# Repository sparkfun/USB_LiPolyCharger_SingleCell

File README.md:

Power_Cell_Lipo_Charger_Booster
===============================
[ 
*USB LiPoly Charger- Single Cell (PRT-12711)*](https://www.sparkfun.com/products/12711)

This is a basic charging circuit that allows you to charger 3.7V LiPo cells at a rate of 500mA or 100mA.
It has a selectable solder jumper, USB input, two pre-installed JST connectors and a barrel jack connector. 

Repository Contents
-------------------

* **/Hardware** - All Eagle design files (.brd, .sch, .STL)
* **/Production** - Test bed files and production panel files

License Information
-------------------
The hardware is released under [Creative Commons ShareAlike 4.0 International](https://creativecommons.org/licenses/by-sa/4.0/).

Distributed as-is; no warranty is given.

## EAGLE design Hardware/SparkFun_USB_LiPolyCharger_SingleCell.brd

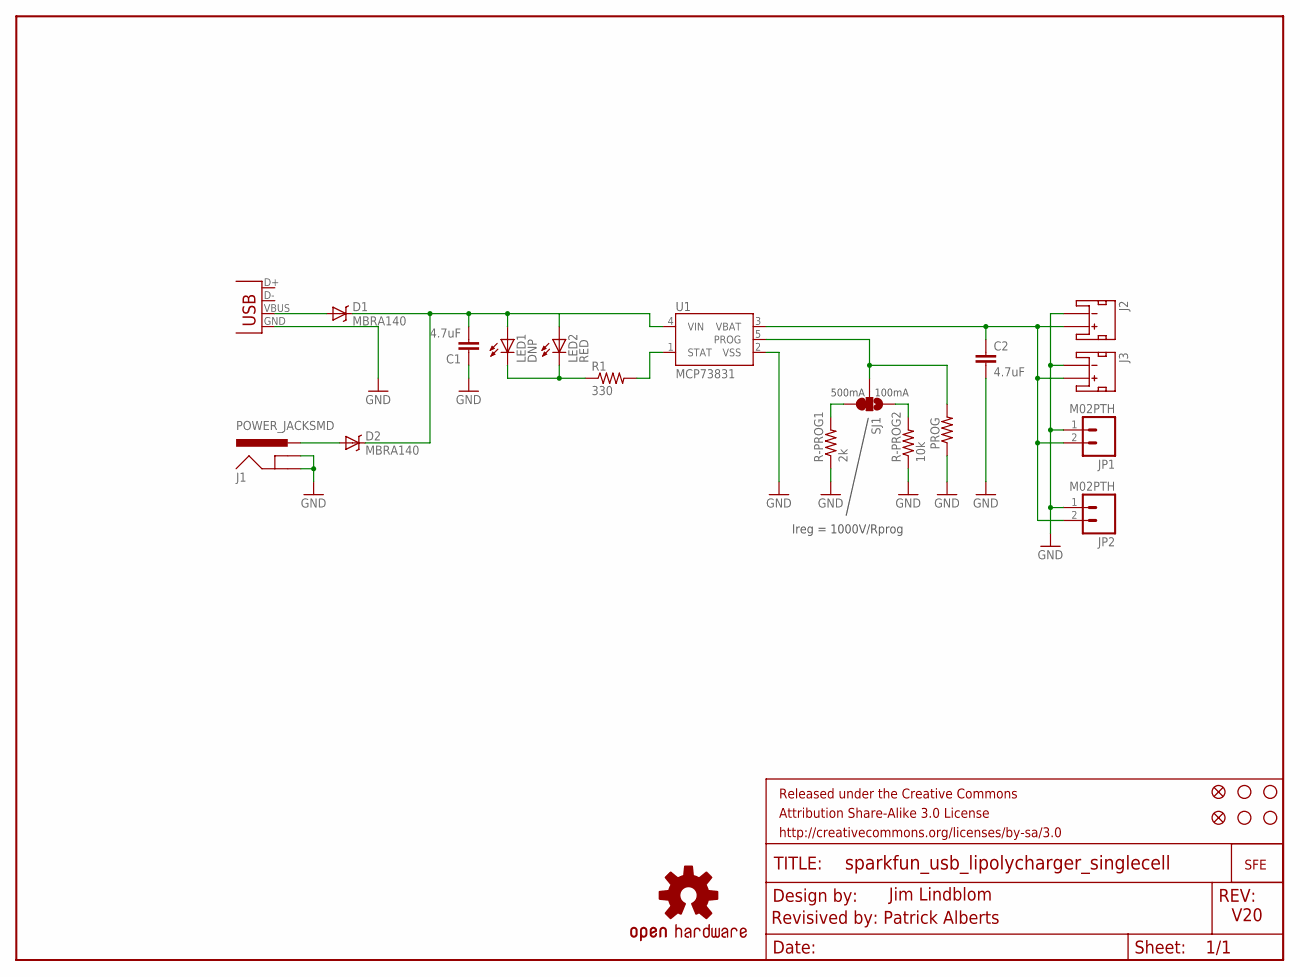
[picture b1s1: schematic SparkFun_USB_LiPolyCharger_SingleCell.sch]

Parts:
C1, C2: 4.7uF; 0603-CAP
D1, D2: MBRA140; SMA-DIODE
FRAME1: FRAME-LETTER; CREATIVE_COMMONS
J1: POWER_JACKSMD; POWER_JACK_SMD
J2, J3: JST_2MM_MALE; JST-2-SMD
JP1, JP2: M02PTH; 1X02
JP7, JP8, JP9, JP10: STAND-OFF
JP11: LOGO-SFENEW; SFE-NEW-WEBLOGO
JP12, JP13: FIDUCIAL1X2; FIDUCIAL-1X2
LED1: DNP; LED3MM
LED2: RED; LED-0603
LOGO1: OSHW-LOGOS; OSHW-LOGO-S
PROG: RESISTORAXIAL-0.3; AXIAL-0.3
R1: 330; 0603-RES
R-PROG1: 2k; 0603-RES
R-PROG2: 10k; 0603-RES
SJ1: SOLDERJUMPER_2WAYS; SJ_3
U1: MCP73831; SOT23-5
X1: USBSMD; USB-MINIB

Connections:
GND: C1.1, C2.2, J1.GND (GNDBREAK), J1.P$4 (GND), J2.1 (-), J3.1 (-), JP1.1, JP2.1, PROG.P$1 (1), R-PROG1.1, R-PROG2.1, U1.2 (VSS), X1.GND
unnamed: C1.2, D1.C, D2.C, LED1.A, LED2.A, U1.4 (VIN)
unnamed: R1.2, U1.1 (STAT)
unnamed: LED1.K (C), LED2.C, R1.1
unnamed: R-PROG1.2, SJ1.3
unnamed: D1.A, X1.VBUS
unnamed: R-PROG2.2, SJ1.1
unnamed: D2.A, J1.VIN0 (PWR)
unnamed: C2.1, J2.2 (+), J3.2 (+), JP1.2, JP2.2, U1.3 (VBAT)
PROG: PROG.P$2 (2), SJ1.2, U1.5 (PROG)

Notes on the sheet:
500mA
100mA
Ireg = 1000V/Rprog
Jim Lindblom
Revisived by: Patrick Alberts
V20

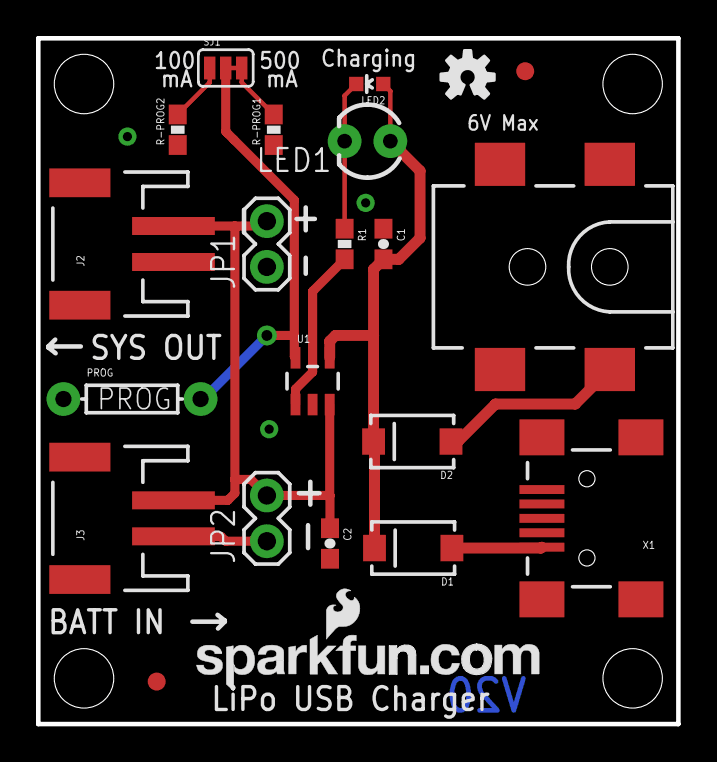
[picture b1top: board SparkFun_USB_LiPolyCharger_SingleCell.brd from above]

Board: 2 copper layers, 35.6 x 38.1 mm, 27 parts (0 on the bottom side), 10 nets.

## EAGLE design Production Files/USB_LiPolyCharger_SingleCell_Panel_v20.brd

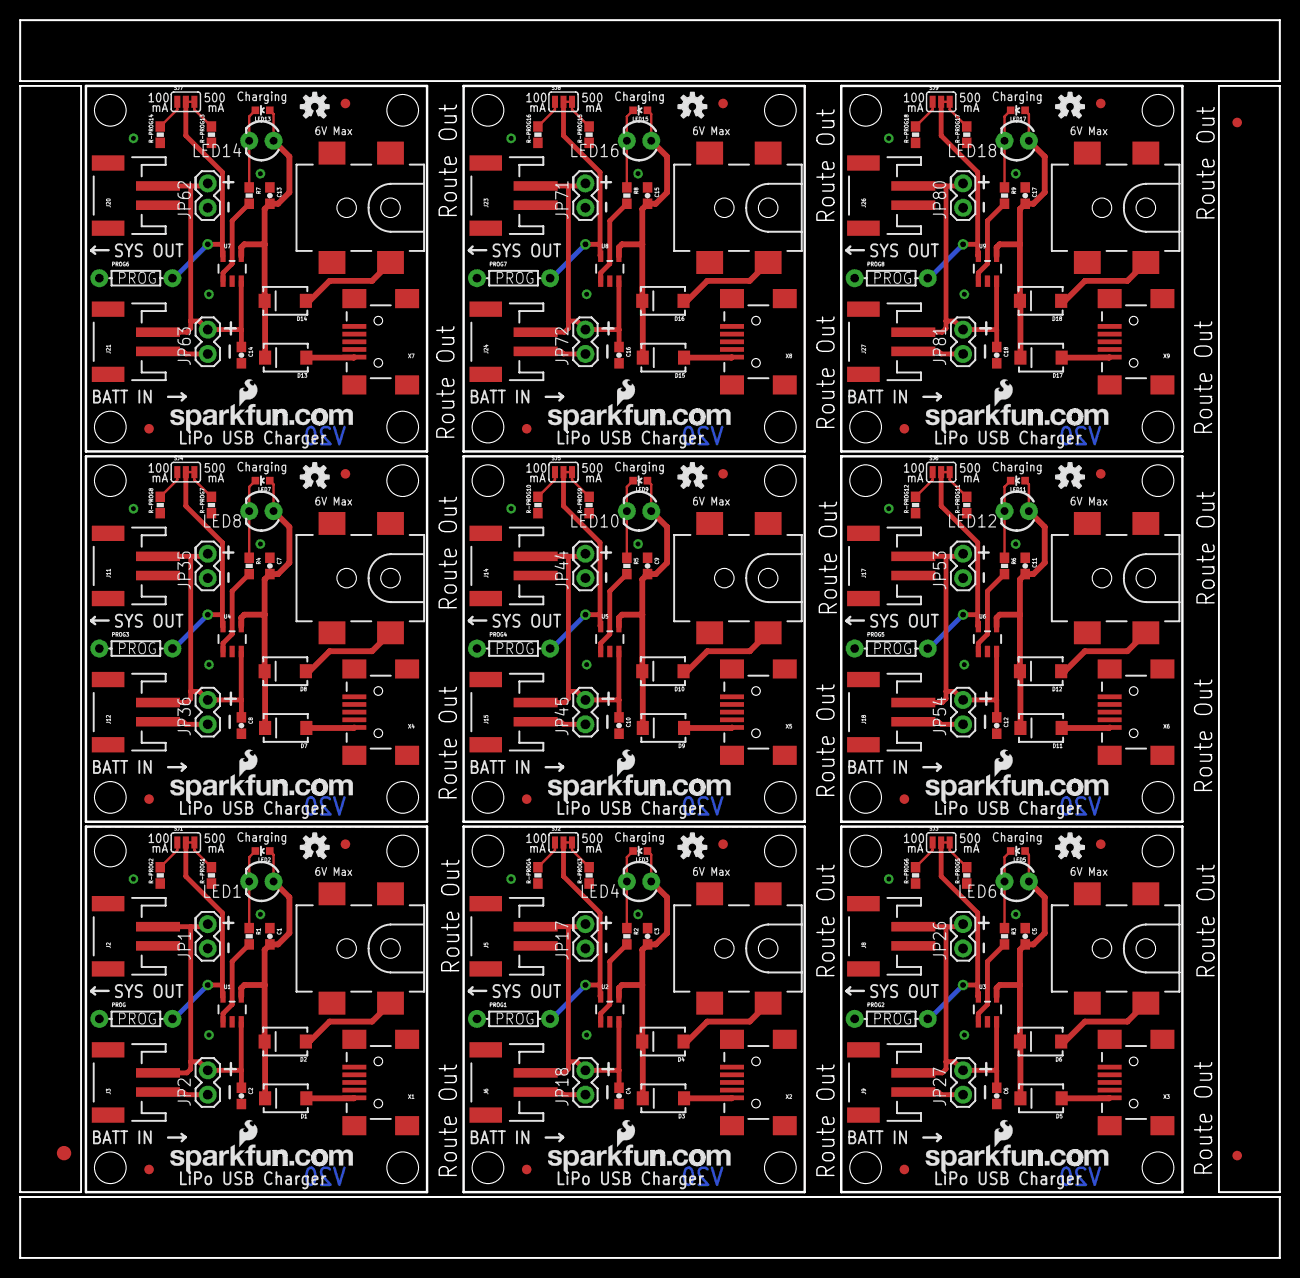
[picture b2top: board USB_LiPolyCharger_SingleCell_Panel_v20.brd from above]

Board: 2 copper layers, 131.3 x 129.0 mm, 237 parts (0 on the bottom side), 90 nets.

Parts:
C1, C2, C3, C4, C5, C6, C7, C8, C9, C10, C11, C12, C13, C14, C15, C16, C17, C18: 4.7uF; 0603-CAP
D1, D2, D3, D4, D5, D6, D7, D8, D9, D10, D11, D12, D13, D14, D15, D16, D17, D18: MBRA140; SMA-DIODE
E$1: FIDUCIAL-1.5X3
E$4, E$5: FIDUCIAL-1X2
J1, J4, J7, J10, J13, J16, J19, J22, J25: POWER_JACKSMD; POWER_JACK_SMD
J2, J3, J5, J6, J8, J9, J11, J12, J14, J15, J17, J18, J20, J21, J23, J24, J26, J27: JST-2-SMD
JP1, JP2, JP17, JP18, JP26, JP27, JP35, JP36, JP44, JP45, JP53, JP54, JP62, JP63, JP71, JP72, JP80, JP81: M02PTH; 1X02
JP3, JP4, JP5, JP6, JP7, JP8, JP9, JP10, JP19, JP20, JP21, JP22, JP28, JP29, JP30, JP31, JP37, JP38, JP39, JP40, JP46, JP47, JP48, JP49, JP55, JP56, JP57, JP58, JP64, JP65, JP66, JP67, JP73, JP74, JP75, JP76: STAND-OFF
JP11, JP14, JP23, JP32, JP41, JP50, JP59, JP68, JP77: LOGO-SFENEW; SFE-NEW-WEBLOGO
JP12, JP13, JP15, JP16, JP24, JP25, JP33, JP34, JP42, JP43, JP51, JP52, JP60, JP61, JP69, JP70, JP78, JP79: FIDUCIAL1X2; FIDUCIAL-1X2
LED1, LED4, LED6, LED8, LED10, LED12, LED14, LED16, LED18: DNP; LED3MM
LED2, LED3, LED5, LED7, LED9, LED11, LED13, LED15, LED17: RED; LED-0603
LOGO1, LOGO2, LOGO3, LOGO4, LOGO5, LOGO6, LOGO7, LOGO8, LOGO9: OSHW-LOGOS; OSHW-LOGO-S
PROG, PROG1, PROG2, PROG3, PROG4, PROG5, PROG6, PROG7, PROG8: AXIAL-0.3
R1, R2, R3, R4, R5, R6, R7, R8, R9: 330; 0603-RES
R-PROG1, R-PROG3, R-PROG5, R-PROG7, R-PROG9, R-PROG11, R-PROG13, R-PROG15, R-PROG17: 2k; 0603-RES
R-PROG2, R-PROG4, R-PROG6, R-PROG8, R-PROG10, R-PROG12, R-PROG14, R-PROG16, R-PROG18: 10k; 0603-RES
SJ1, SJ2, SJ3, SJ4, SJ5, SJ6, SJ7, SJ8, SJ9: SJ_3
U1, U2, U3, U4, U5, U6, U7, U8, U9: MCP73831; SOT23-5
X1, X2, X3, X4, X5, X6, X7, X8, X9: USBSMD; USB-MINIB

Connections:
GND: C1.1, C2.2, J1.GND, J1.P$4, J2.1, J3.1, JP1.1, JP2.1, PROG.P$1, R-PROG1.1, R-PROG2.1, U1.2, X1.GND
GND1: C3.1, C4.2, J4.GND, J4.P$4, J5.1, J6.1, JP17.1, JP18.1, PROG1.P$1, R-PROG3.1, R-PROG4.1, U2.2, X2.GND
GND2: C5.1, C6.2, J7.GND, J7.P$4, J8.1, J9.1, JP26.1, JP27.1, PROG2.P$1, R-PROG5.1, R-PROG6.1, U3.2, X3.GND
GND3: C7.1, C8.2, J10.GND, J10.P$4, J11.1, J12.1, JP35.1, JP36.1, PROG3.P$1, R-PROG7.1, R-PROG8.1, U4.2, X4.GND
GND4: C9.1, C10.2, J13.GND, J13.P$4, J14.1, J15.1, JP44.1, JP45.1, PROG4.P$1, R-PROG9.1, R-PROG10.1, U5.2, X5.GND
GND5: C11.1, C12.2, J16.GND, J16.P$4, J17.1, J18.1, JP53.1, JP54.1, PROG5.P$1, R-PROG11.1, R-PROG12.1, U6.2, X6.GND
GND6: C13.1, C14.2, J19.GND, J19.P$4, J20.1, J21.1, JP62.1, JP63.1, PROG6.P$1, R-PROG13.1, R-PROG14.1, U7.2, X7.GND
GND7: C15.1, C16.2, J22.GND, J22.P$4, J23.1, J24.1, JP71.1, JP72.1, PROG7.P$1, R-PROG15.1, R-PROG16.1, U8.2, X8.GND
GND8: C17.1, C18.2, J25.GND, J25.P$4, J26.1, J27.1, JP80.1, JP81.1, PROG8.P$1, R-PROG17.1, R-PROG18.1, U9.2, X9.GND
unnamed: C1.2, D1.C, D2.C, LED1.A, LED2.A, U1.4
unnamed: R1.2, U1.1
unnamed: LED1.K, LED2.C, R1.1
unnamed: R-PROG1.2, SJ1.3
unnamed: D1.A, X1.VBUS
unnamed: R-PROG2.2, SJ1.1
unnamed: D2.A, J1.VIN0
unnamed: C3.2, D3.C, D4.C, LED3.A, LED4.A, U2.4
unnamed: C2.1, J2.2, J3.2, JP1.2, JP2.2, U1.3
unnamed: R-PROG4.2, SJ2.1
unnamed: R-PROG3.2, SJ2.3
unnamed: R2.2, U2.1
unnamed: LED3.C, LED4.K, R2.1
unnamed: D3.A, X2.VBUS
unnamed: C4.1, J5.2, J6.2, JP17.2, JP18.2, U2.3
unnamed: D4.A, J4.VIN0
unnamed: C5.2, D5.C, D6.C, LED5.A, LED6.A, U3.4
unnamed: R-PROG6.2, SJ3.1
unnamed: R-PROG5.2, SJ3.3
unnamed: R3.2, U3.1
unnamed: LED5.C, LED6.K, R3.1
unnamed: D5.A, X3.VBUS
unnamed: C6.1, J8.2, J9.2, JP26.2, JP27.2, U3.3
unnamed: D6.A, J7.VIN0
unnamed: C7.2, D7.C, D8.C, LED7.A, LED8.A, U4.4
unnamed: R-PROG8.2, SJ4.1
unnamed: R-PROG7.2, SJ4.3
unnamed: R4.2, U4.1
unnamed: LED7.C, LED8.K, R4.1
unnamed: D7.A, X4.VBUS
unnamed: C8.1, J11.2, J12.2, JP35.2, JP36.2, U4.3
unnamed: D8.A, J10.VIN0
unnamed: C9.2, D9.C, D10.C, LED9.A, LED10.A, U5.4
unnamed: R-PROG10.2, SJ5.1
unnamed: R-PROG9.2, SJ5.3
unnamed: R5.2, U5.1
unnamed: LED9.C, LED10.K, R5.1
unnamed: D9.A, X5.VBUS
unnamed: C10.1, J14.2, J15.2, JP44.2, JP45.2, U5.3
unnamed: D10.A, J13.VIN0
unnamed: C11.2, D11.C, D12.C, LED11.A, LED12.A, U6.4
unnamed: R-PROG12.2, SJ6.1
unnamed: R-PROG11.2, SJ6.3
unnamed: R6.2, U6.1
unnamed: LED11.C, LED12.K, R6.1
unnamed: D11.A, X6.VBUS
unnamed: C12.1, J17.2, J18.2, JP53.2, JP54.2, U6.3
unnamed: D12.A, J16.VIN0
unnamed: C13.2, D13.C, D14.C, LED13.A, LED14.A, U7.4
unnamed: R-PROG14.2, SJ7.1
unnamed: R-PROG13.2, SJ7.3
unnamed: R7.2, U7.1
unnamed: LED13.C, LED14.K, R7.1
unnamed: D13.A, X7.VBUS
unnamed: C14.1, J20.2, J21.2, JP62.2, JP63.2, U7.3
unnamed: D14.A, J19.VIN0
unnamed: C15.2, D15.C, D16.C, LED15.A, LED16.A, U8.4
unnamed: R-PROG16.2, SJ8.1
unnamed: R-PROG15.2, SJ8.3
unnamed: R8.2, U8.1
unnamed: LED15.C, LED16.K, R8.1
unnamed: D15.A, X8.VBUS
unnamed: C16.1, J23.2, J24.2, JP71.2, JP72.2, U8.3
unnamed: D16.A, J22.VIN0
unnamed: C17.2, D17.C, D18.C, LED17.A, LED18.A, U9.4
unnamed: R-PROG18.2, SJ9.1
unnamed: R-PROG17.2, SJ9.3
unnamed: R9.2, U9.1
unnamed: LED17.C, LED18.K, R9.1
unnamed: D17.A, X9.VBUS
unnamed: C18.1, J26.2, J27.2, JP80.2, JP81.2, U9.3
unnamed: D18.A, J25.VIN0
PROG: PROG.P$2, SJ1.2, U1.5
PROG1: PROG1.P$2, SJ2.2, U2.5
PROG2: PROG2.P$2, SJ3.2, U3.5
PROG3: PROG3.P$2, SJ4.2, U4.5
PROG4: PROG4.P$2, SJ5.2, U5.5
PROG5: PROG5.P$2, SJ6.2, U6.5
PROG6: PROG6.P$2, SJ7.2, U7.5
PROG7: PROG7.P$2, SJ8.2, U8.5
PROG8: PROG8.P$2, SJ9.2, U9.5

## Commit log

2013-09-23 Board File/Gitignore Commit
    Added the brd /sch files and the gitignore
2013-09-24 Added Barrel Jack
    Added the barrel jack, sorry for the extra commit, needed to get this
    sync before I work out on the road.
2013-11-20 Added Diodes/Prog RES
    Added 2x MBRA diodes to the power lines of the USB and Barrel jack .
    Also added an optional PTH res for the PROG line.
2014-01-20 Sch Cleanup
2014-01-21 Fixed Airwire
2014-01-21 Created Panel
2014-11-05 Updating README with product links

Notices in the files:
parts and their libraries:
SparkFun-DiscreteSemi: Licensing: CC v3.0 Share-Alike You are welcome to use this library for commercial purposes.
SparkFun-Aesthetics: Released under the Creative Commons Attribution Share-Alike 3.0 License
SparkFun-Aesthetics: http://creativecommons.org/licenses/by-sa/3.0
